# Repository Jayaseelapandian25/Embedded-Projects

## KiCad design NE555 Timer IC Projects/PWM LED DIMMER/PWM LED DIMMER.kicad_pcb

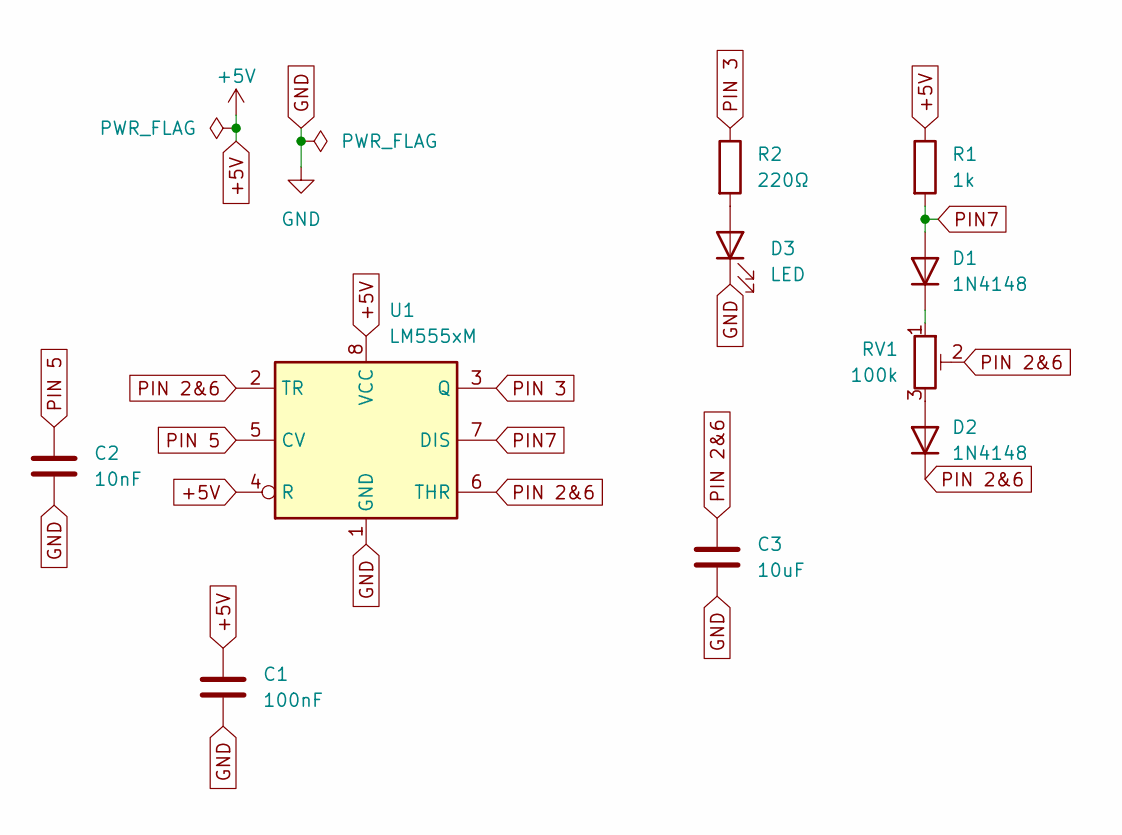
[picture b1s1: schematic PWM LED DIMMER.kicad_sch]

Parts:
C1: 100nF; C_0805_2012Metric_Pad1.18x1.45mm_HandSolder
C2: 10nF; C_0805_2012Metric_Pad1.18x1.45mm_HandSolder
C3: 10uF; C_0805_2012Metric_Pad1.18x1.45mm_HandSolder
D1, D2: 1N4148; D_SOD-123
D3: LED; LED_0805_2012Metric_Pad1.15x1.40mm_HandSolder
R1: 1k; R_0805_2012Metric_Pad1.20x1.40mm_HandSolder
R2: 220Ω; R_0805_2012Metric_Pad1.20x1.40mm_HandSolder
RV1: 100k; Potentiometer_Bourns_3296W_Vertical
U1: LM555xM; SOIC-8_3.9x4.9mm_P1.27mm

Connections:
+5V: C1.1, R1.1, U1.4 (R), U1.8 (VCC)
GND: C1.2, C2.2, C3.2, D3.1 (K), U1.1 (GND)
unnamed: D1.1 (K), RV1.1
unnamed: D2.2 (A), RV1.3
unnamed: D3.2 (A), R2.2
PIN7: D1.2 (A), R1.2, U1.7 (DIS)
PIN 2&6: C3.1, D2.1 (K), RV1.2, U1.2 (TR), U1.6 (THR)
PIN 3: R2.1, U1.3 (Q)
PIN 5: C2.1, U1.5 (CV)

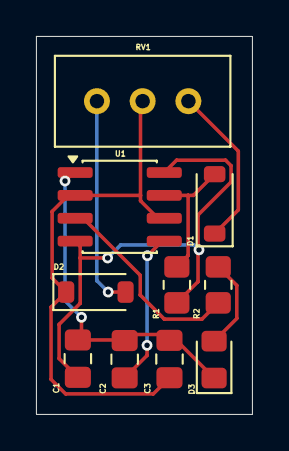
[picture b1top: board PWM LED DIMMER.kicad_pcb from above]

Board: 2 copper layers, 12.0 x 21.0 mm, 10 parts (0 on the bottom side), 9 nets.

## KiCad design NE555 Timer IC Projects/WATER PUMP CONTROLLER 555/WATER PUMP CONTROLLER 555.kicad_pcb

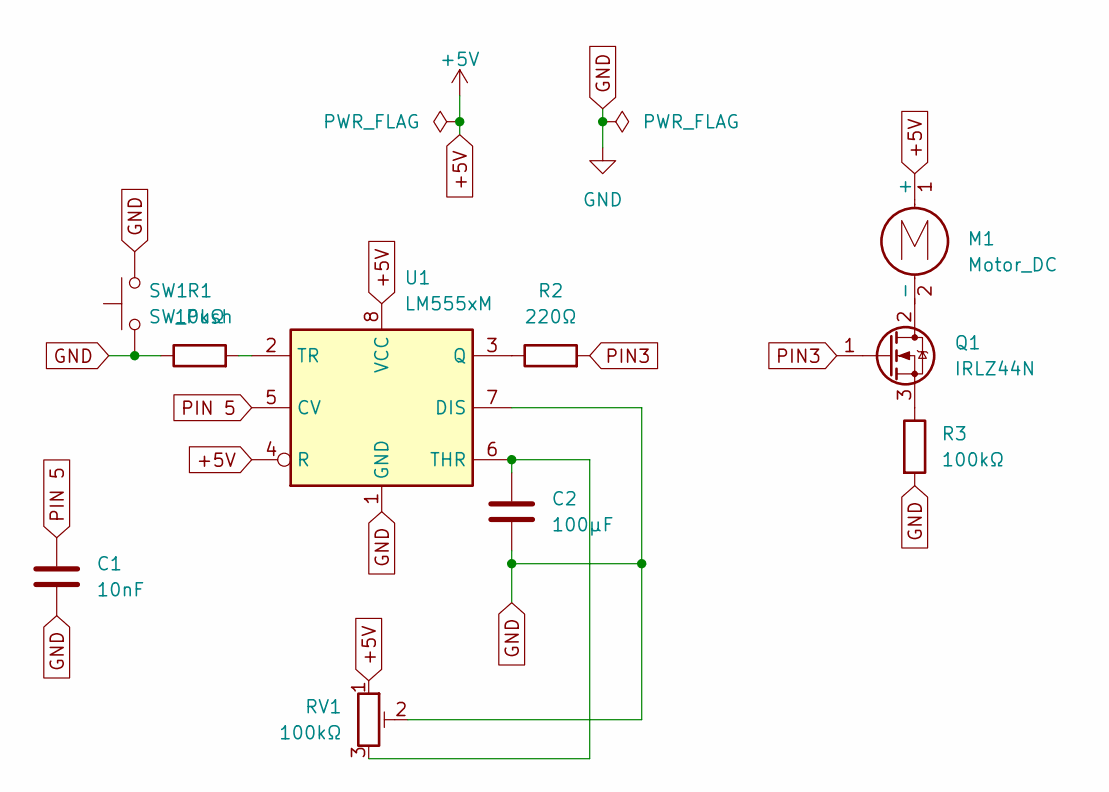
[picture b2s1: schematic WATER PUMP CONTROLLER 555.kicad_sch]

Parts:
C1: 10nF; C_0805_2012Metric
C2: 100µF; C_0805_2012Metric
M1: Motor_DC; JST_PH_B2B-PH-K_1x02_P2.00mm_Vertical
Q1: IRLZ44N; TO-220-3_Vertical
R1: 10kΩ; R_0805_2012Metric
R2: 220Ω; R_0805_2012Metric
R3: 100kΩ; R_0805_2012Metric
RV1: 100kΩ; Potentiometer_Bourns_3296W_Vertical
SW1: SW_Push; SW_SPST_TL3342
U1: LM555xM; SOIC-8_3.9x4.9mm_P1.27mm

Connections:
+5V: M1.1 (+), RV1.1, U1.4 (R), U1.8 (VCC)
GND: C1.2, C2.2, R1.1, R3.2, RV1.2, SW1.1, SW1.2, U1.1 (GND), U1.7 (DIS)
unnamed: M1.2 (-), Q1.2 (D)
unnamed: Q1.3 (S), R3.1
unnamed: R2.1, U1.3 (Q)
unnamed: C2.1, RV1.3, U1.6 (THR)
unnamed: R1.2, U1.2 (TR)
PIN3: Q1.1 (G), R2.2
PIN 5: C1.1, U1.5 (CV)

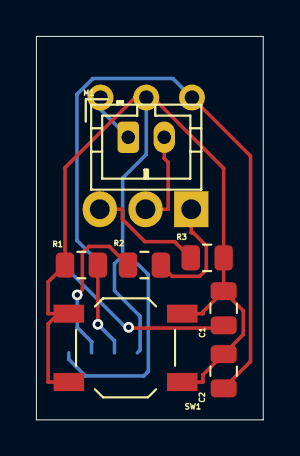
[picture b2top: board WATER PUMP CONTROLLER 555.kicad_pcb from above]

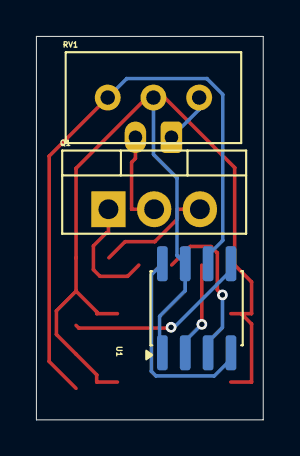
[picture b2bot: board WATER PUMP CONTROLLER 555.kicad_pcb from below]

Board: 2 copper layers, 12.6 x 21.3 mm, 10 parts (3 on the bottom side), 9 nets.

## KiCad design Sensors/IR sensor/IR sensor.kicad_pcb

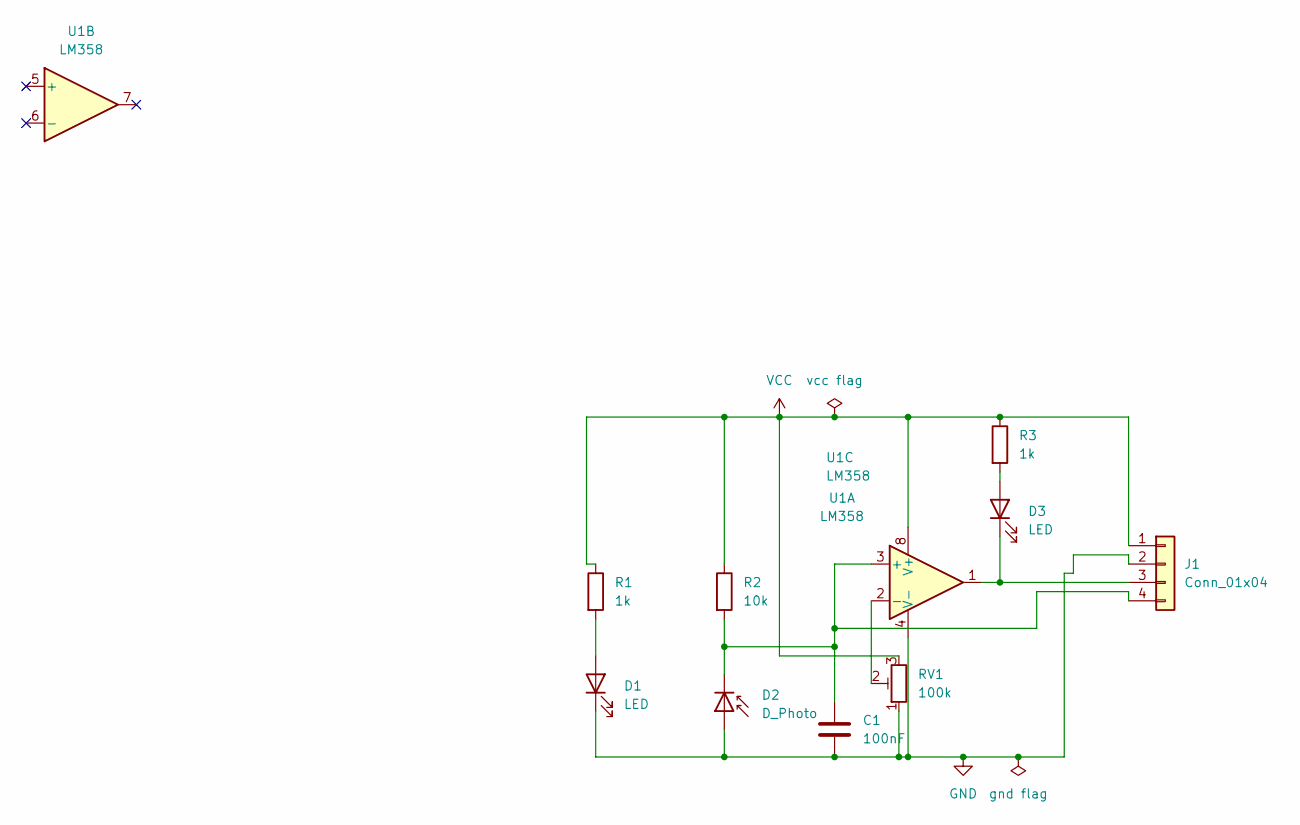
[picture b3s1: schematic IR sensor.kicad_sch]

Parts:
C1: 100nF; C_0805_2012Metric_Pad1.18x1.45mm_HandSolder
D1, D3: LED; LED_0805_2012Metric
D2: D_Photo; LED_D5.0mm
J1: Conn_01x04; PinHeader_1x04_P1.00mm_Vertical
R1, R3: 1k; R_0805_2012Metric_Pad1.20x1.40mm_HandSolder
R2: 10k; R_0805_2012Metric_Pad1.20x1.40mm_HandSolder
RV1: 100k; Potentiometer_Bourns_3296W_Vertical
U1: LM358; DIP-8_W7.62mm

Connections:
GND: C1.2, D1.1 (K), D2.2 (A), J1.2, RV1.1, U1.4 (V-)
unnamed: D1.2 (A), R1.2
unnamed: C1.1, D2.1 (K), J1.4, R2.2, U1.3 (+)
unnamed: D3.2 (A), R3.2
unnamed: D3.1 (K), J1.3, U1.1
unnamed: RV1.2, U1.2 (-)
VCC: J1.1, R1.1, R2.1, R3.1, RV1.3, U1.8 (V+)

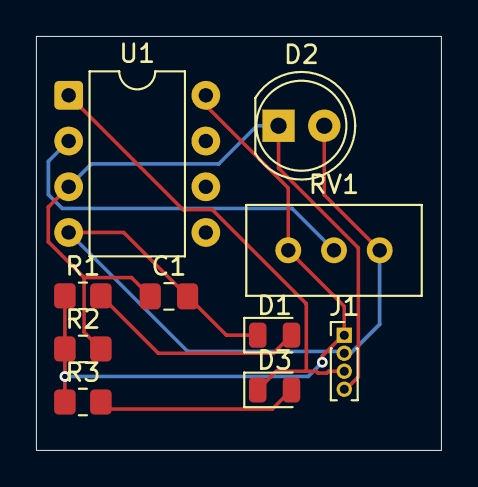
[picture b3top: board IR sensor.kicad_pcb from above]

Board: 2 copper layers, 22.5 x 23.0 mm, 10 parts (0 on the bottom side), 7 nets.

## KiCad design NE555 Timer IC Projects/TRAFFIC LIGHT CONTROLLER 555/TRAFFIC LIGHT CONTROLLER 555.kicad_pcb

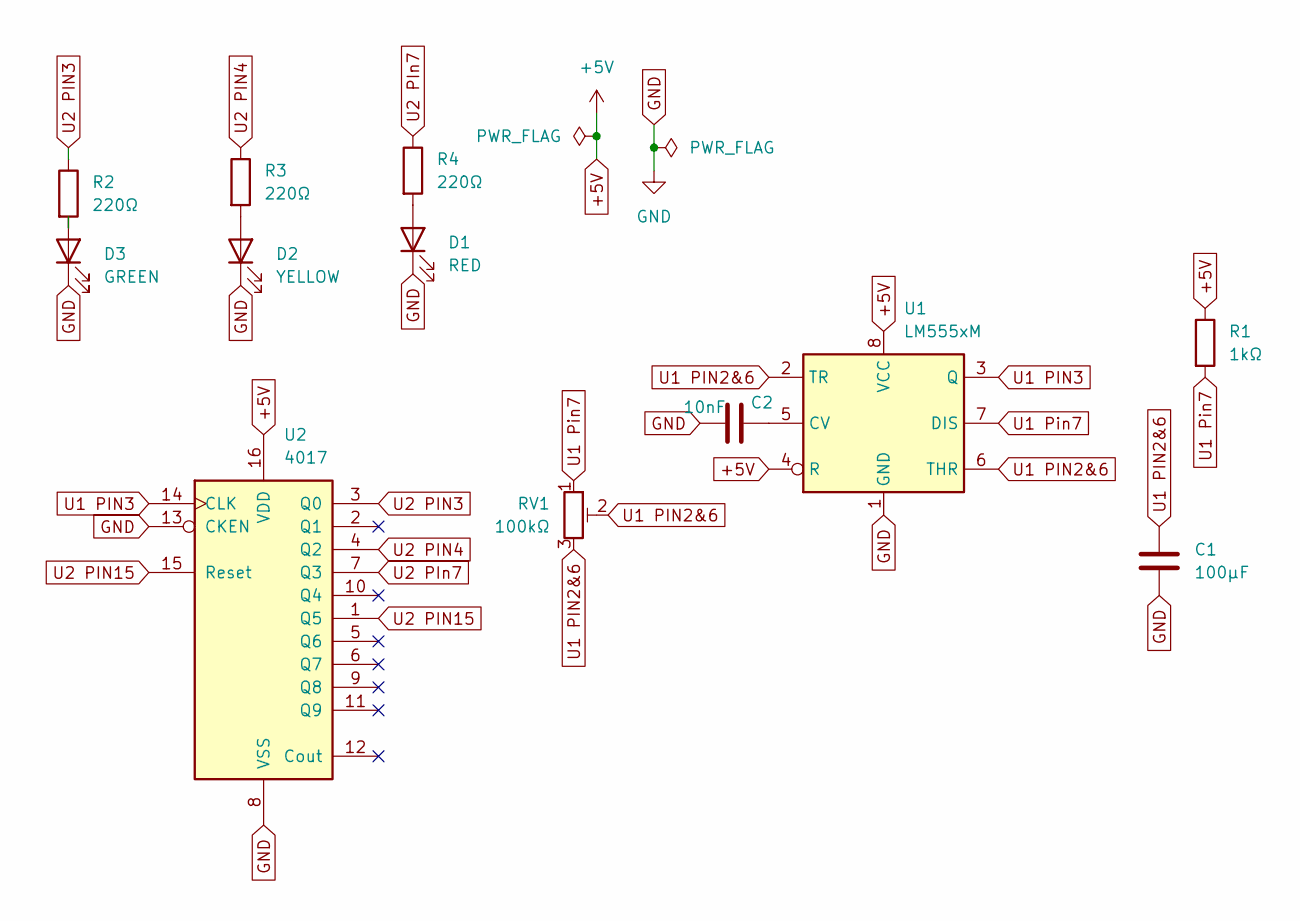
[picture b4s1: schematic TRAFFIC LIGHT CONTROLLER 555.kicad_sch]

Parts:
C1: 100µF; CP_Elec_5x5.4
C2: 10nF; C_0805_2012Metric
D1: RED; LED_0805_2012Metric
D2: YELLOW; LED_0805_2012Metric
D3: GREEN; LED_0805_2012Metric
R1: 1kΩ; R_0805_2012Metric
R2, R3, R4: 220Ω; R_0805_2012Metric
RV1: 100kΩ; Potentiometer_Bourns_3296W_Vertical
U1: LM555xM; SOIC-8_3.9x4.9mm_P1.27mm
U2: 4017; SOIC-16_3.9x9.9mm_P1.27mm

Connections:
+5V: R1.1, U1.4 (R), U1.8 (VCC), U2.16 (VDD)
GND: C1.2, C2.2, D1.1 (K), D2.1 (K), D3.1 (K), U1.1 (GND), U2.8 (VSS), U2.13 (CKEN)
unnamed: D1.2 (A), R4.2
unnamed: D2.2 (A), R3.2
unnamed: D3.2 (A), R2.2
unnamed: C2.1, U1.5 (CV)
U1 PIN2&6: C1.1, RV1.2, RV1.3, U1.2 (TR), U1.6 (THR)
U1 PIN3: U1.3 (Q), U2.14 (CLK)
U1 Pin7: R1.2, RV1.1, U1.7 (DIS)
U2 PIN3: R2.1, U2.3 (Q0)
U2 PIN4: R3.1, U2.4 (Q2)
U2 PIN15: U2.1 (Q5), U2.15 (Reset)
U2 PIn7: R4.1, U2.7 (Q3)

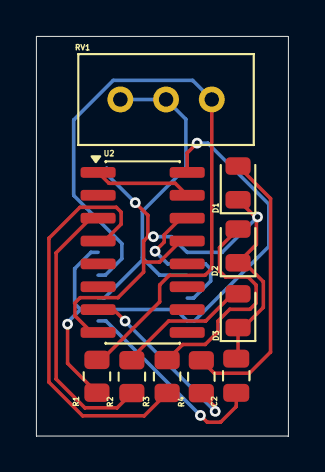
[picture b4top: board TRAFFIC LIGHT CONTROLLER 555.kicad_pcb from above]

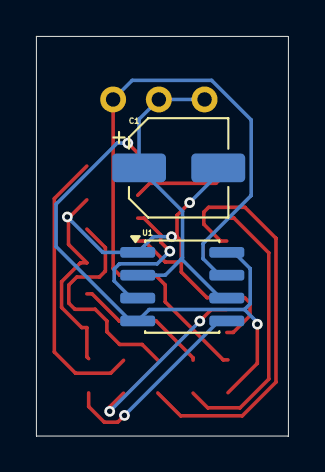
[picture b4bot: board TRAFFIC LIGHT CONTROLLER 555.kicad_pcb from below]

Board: 2 copper layers, 14.0 x 22.2 mm, 12 parts (2 on the bottom side), 13 nets.

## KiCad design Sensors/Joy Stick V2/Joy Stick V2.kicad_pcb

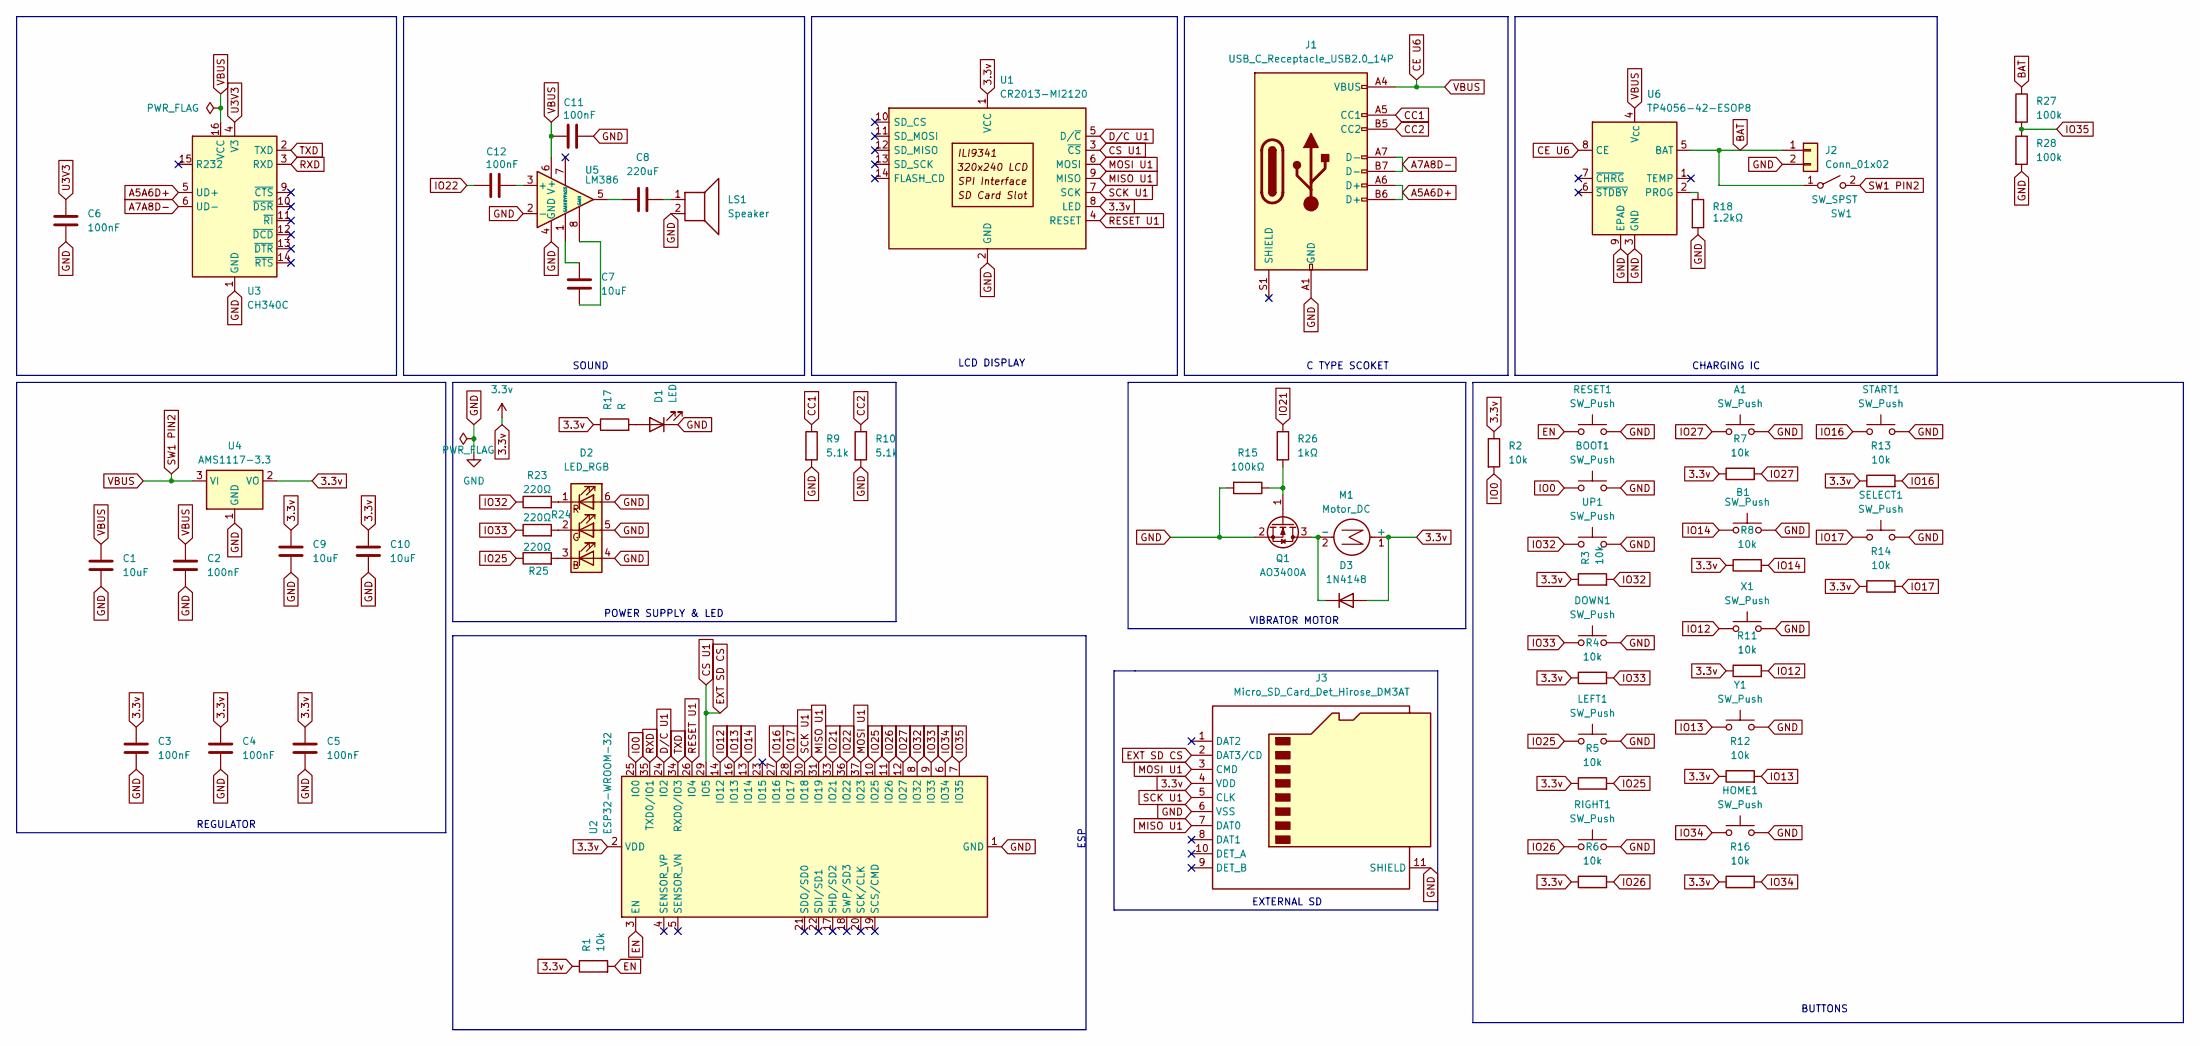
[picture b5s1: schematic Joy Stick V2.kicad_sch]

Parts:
A1: SW_Push; SW_SPST_TL3342
B1: SW_Push; SW_SPST_TL3342
BOOT1: SW_Push; SW_SPST_TL3342
C1, C7, C9, C10: 10uF; C_0805_2012Metric
C2, C3, C4, C5, C6, C11, C12: 100nF; C_0805_2012Metric
C8: 220uF; C_0805_2012Metric
D1: LED; LED_0805_2012Metric
D2: LED_RGB; LED_RGB_5050-6
D3: 1N4148; D_SOD-123
DOWN1: SW_Push; SW_SPST_TL3342
HOME1: SW_Push; SW_SPST_TL3342
J1: USB_C_Receptacle_USB2.0_14P; USB_C_Receptacle_HRO_TYPE-C-31-M-12
J2: Conn_01x02; JST_PH_S2B-PH-K_1x02_P2.00mm_Horizontal
J3: Micro_SD_Card_Det_Hirose_DM3AT; microSD_HC_Hirose_DM3AT-SF-PEJM5
LEFT1: SW_Push; SW_SPST_TL3342
LS1: Speaker; JST_PH_S2B-PH-K_1x02_P2.00mm_Horizontal
M1: Motor_DC; JST_PH_S2B-PH-K_1x02_P2.00mm_Horizontal
Q1: AO3400A; SOT-23
R1, R2, R3, R4, R5, R6, R7, R8, R11, R12, R13, R14, R16: 10k; R_0805_2012Metric
R9, R10: 5.1k; R_0805_2012Metric
R15: 100kΩ; R_0805_2012Metric
R17: R; R_0805_2012Metric
R18: 1.2kΩ; R_0805_2012Metric
R23, R24, R25: 220Ω; R_0805_2012Metric
R26: 1kΩ; R_0805_2012Metric
R27, R28: 100k; R_0805_2012Metric
RESET1: SW_Push; SW_SPST_TL3342
RIGHT1: SW_Push; SW_SPST_TL3342
SELECT1: SW_Push; SW_SPST_TL3342
START1: SW_Push; SW_SPST_TL3342
SW1: SW_SPST; SW_SPST_TL3342
U1: CR2013-MI2120
U2: ESP32-WROOM-32
U3: CH340C; SOIC-16_3.9x9.9mm_P1.27mm
U4: AMS1117-3.3; SOT-223-3_TabPin2
U5: LM386; SOIC-8_3.9x4.9mm_P1.27mm
U6: TP4056-42-ESOP8; SOIC-8-1EP_3.9x4.9mm_P1.27mm_EP2.41x3.3mm_ThermalVias
UP1: SW_Push; SW_SPST_TL3342
X1: SW_Push; SW_SPST_TL3342
Y1: SW_Push; SW_SPST_TL3342

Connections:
3.3v: C3.1, C4.1, C5.1, C9.1, C10.1, D3.2 (A), J3.4 (VDD), M1.1 (+), R1.1, R2.1, R3.1, R4.1, R5.1, R6.1, R7.1, R8.1, R11.1, R12.1, R13.1, R14.1, R16.1, R17.1, U1.1 (VCC), U1.8 (LED), U2.2 (VDD), U4.2 (VO)
A5A6D+: J1.A6 (D+), J1.B6 (D+), U3.5 (UD+)
A7A8D-: J1.A7 (D-), J1.B7 (D-), U3.6 (UD-)
BAT: J2.1, R27.1, SW1.1 (A), U6.5 (BAT)
CC1: J1.A5 (CC1), R9.1
CC2: J1.B5 (CC2), R10.1
CE U6: C1.1, C2.1, C11.1, J1.A4 (VBUS), J1.A9 (VBUS), J1.B4 (VBUS), J1.B9 (VBUS), SW1.2 (B), U3.16 (VCC), U4.3 (VI), U5.6 (V+), U6.4 (V_{CC}), U6.8 (CE)
CS U1: J3.2 (DAT3/CD), U1.3 (~CS), U2.29 (IO5)
D/C U1: U1.5 (D/~C), U2.24 (IO2)
EN: R1.2, RESET1.1, U2.3 (EN)
GND: A1.2, B1.2, BOOT1.2, C1.2, C2.2, C3.2, C4.2, C5.2, C6.2, C9.2, C10.2, C11.2, D1.1 (K), D2.4 (BA), D2.5 (GA), D2.6 (RA), DOWN1.2, HOME1.2, J1.A1 (GND), J1.A12 (GND), J1.B1 (GND), J1.B12 (GND), J2.2, J3.6 (VSS), J3.11 (SHIELD), LEFT1.2, LS1.2, Q1.2 (S), R9.2, R10.2, R15.2, R18.2, R28.2, RESET1.2, RIGHT1.2, SELECT1.2, START1.2, U1.2 (GND), U2.1 (GND), U2.15 (GND), U2.38 (GND), U2.39 (GND), U3.1 (GND), U4.1 (GND), U5.2 (-), U5.4 (GND), U6.3 (GND), U6.9 (EPAD), UP1.2, X1.2, Y1.2
IO0: BOOT1.1, R2.2, U2.25 (IO0)
IO12: R11.2, U2.14 (IO12), X1.1
IO13: R12.2, U2.16 (IO13), Y1.1
IO14: B1.1, R8.2, U2.13 (IO14)
IO16: R13.2, START1.1, U2.27 (IO16)
IO17: R14.2, SELECT1.1, U2.28 (IO17)
IO21: R26.1, U2.33 (IO21)
IO22: C12.1, U2.36 (IO22)
IO25: LEFT1.1, R5.2, R25.1, U2.10 (IO25)
IO26: R6.2, RIGHT1.1, U2.11 (IO26)
IO27: A1.1, R7.2, U2.12 (IO27)
IO32: R3.2, R23.1, U2.8 (IO32), UP1.1
IO33: DOWN1.1, R4.2, R24.1, U2.9 (IO33)
IO34: HOME1.1, R16.2, U2.6 (IO34)
IO35: R27.2, R28.1, U2.7 (IO35)
MISO U1: J3.7 (DAT0), U1.9 (MISO), U2.31 (IO19)
MOSI U1: J3.3 (CMD), U1.6 (MOSI), U2.37 (IO23)
unnamed: C7.1, U5.1 (GAIN)
unnamed: C7.2, U5.8 (GAIN)
unnamed: C8.1, U5.5
unnamed: C8.2, LS1.1
unnamed: D1.2 (A), R17.2
unnamed: D2.3 (BK), R25.2
unnamed: D2.2 (GK), R24.2
unnamed: D2.1 (RK), R23.2
unnamed: D3.1 (K), M1.2 (-), Q1.3 (D)
unnamed: Q1.1 (G), R15.1, R26.2
unnamed: C12.2, U5.3 (+)
unnamed: R18.1, U6.2 (PROG)
RESET U1: U1.4 (RESET), U2.26 (IO4)
RXD: U2.35 (TXD0/IO1), U3.3 (RXD)
SCK U1: J3.5 (CLK), U1.7 (SCK), U2.30 (IO18)
TXD: U2.34 (RXD0/IO3), U3.2 (TXD)
U3V3: C6.1, U3.4 (V3)

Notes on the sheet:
BUTTONS
POWER SUPPLY & LED
C TYPE SCOKET
CHARGING IC
VIBRATOR MOTOR
ESP
EXTERNAL SD
LCD DISPLAY
REGULATOR
SOUND

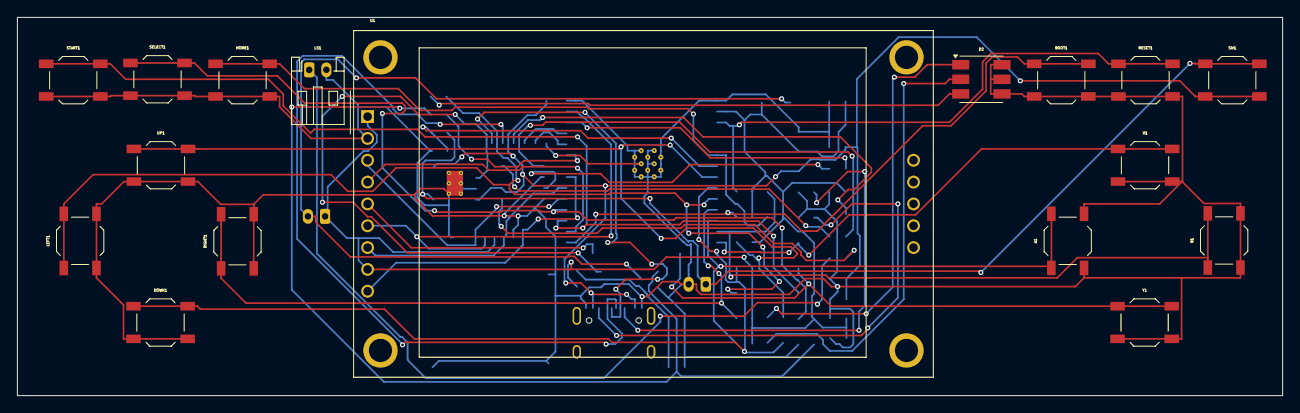
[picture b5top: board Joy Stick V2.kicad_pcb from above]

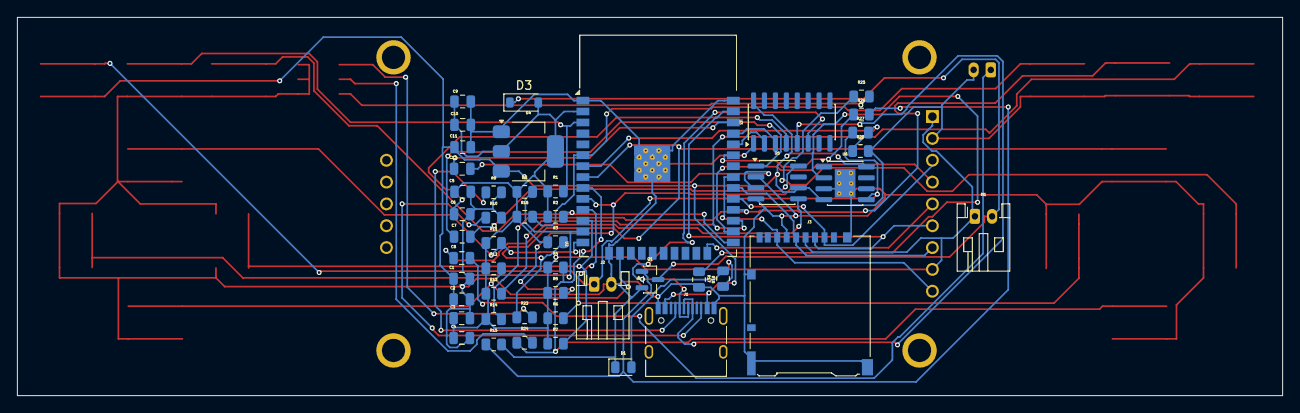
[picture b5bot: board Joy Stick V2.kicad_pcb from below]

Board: 2 copper layers, 147.2 x 44.0 mm, 65 parts (48 on the bottom side), 45 nets.

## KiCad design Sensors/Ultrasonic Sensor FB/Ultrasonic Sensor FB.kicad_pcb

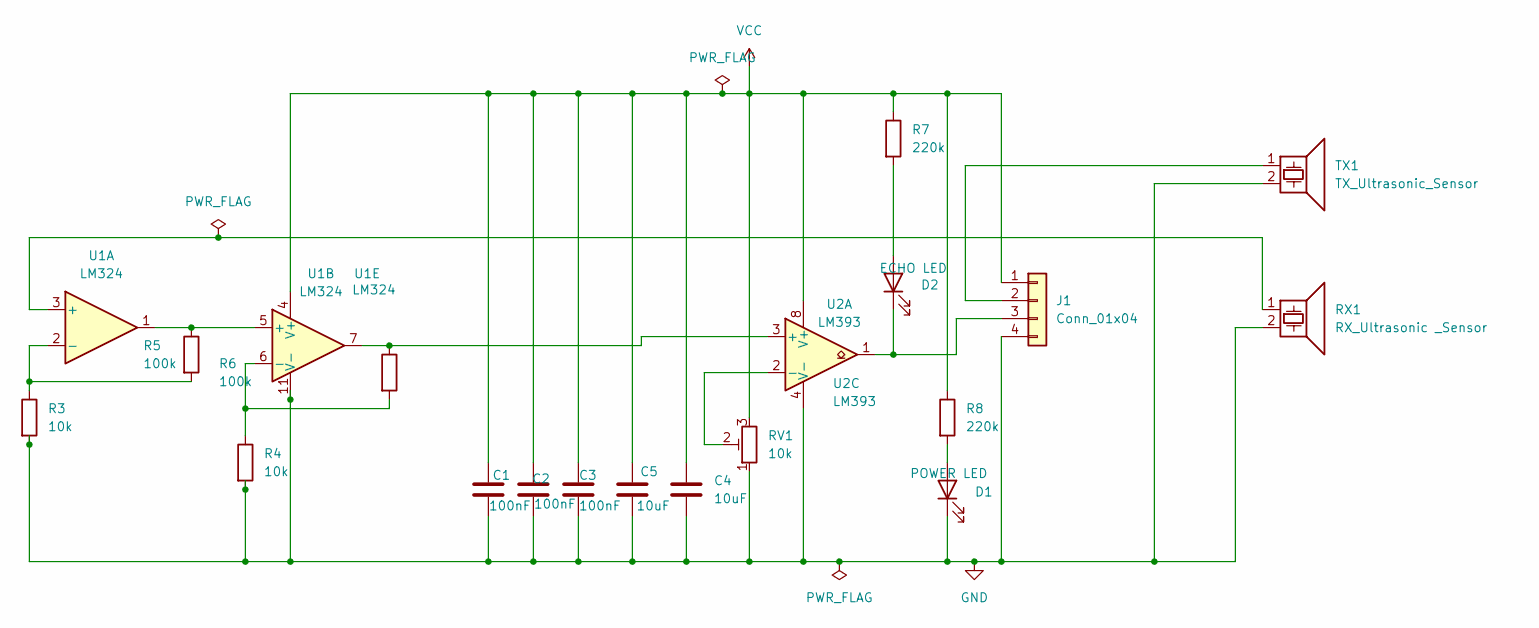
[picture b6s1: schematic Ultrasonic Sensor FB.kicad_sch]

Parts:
C1, C2, C3: 100nF; C_0805_2012Metric_Pad1.18x1.45mm_HandSolder
C4, C5: 10uF; C_0805_2012Metric_Pad1.18x1.45mm_HandSolder
D1: POWER LED; LED_0805_2012Metric_Pad1.15x1.40mm_HandSolder
D2: ECHO LED; LED_0805_2012Metric_Pad1.15x1.40mm_HandSolder
J1: Conn_01x04; PinHeader_1x04_P2.54mm_Vertical
R3, R4: 10k; R_0805_2012Metric_Pad1.20x1.40mm_HandSolder
R5, R6: 100k; R_0805_2012Metric_Pad1.20x1.40mm_HandSolder
R7, R8: 220k; R_0805_2012Metric_Pad1.20x1.40mm_HandSolder
RV1: 10k; Potentiometer_Bourns_3214X_Vertical
RX1: RX_Ultrasonic _Sensor; Buzzer_12x9.5RM7.6
TX1: TX_Ultrasonic_Sensor; Buzzer_12x9.5RM7.6
U1: LM324; SOIC-14_3.9x8.7mm_P1.27mm
U2: LM393; SOIC-8_3.9x4.9mm_P1.27mm

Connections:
GND: C1.2, C2.2, C3.2, C4.2, C5.2, D1.1 (K), J1.4, R3.2, R4.2, RV1.1, RX1.2, TX1.2, U1.11 (V-), U2.4 (V-)
unnamed: D1.2 (A), R8.2
unnamed: D2.2 (A), R7.2
unnamed: D2.1 (K), J1.3, U2.1
unnamed: J1.2, TX1.1
unnamed: RX1.1, U1.3 (+)
unnamed: R3.1, R5.2, U1.2 (-)
unnamed: R5.1, U1.1, U1.5 (+)
unnamed: R4.1, R6.2, U1.6 (-)
unnamed: R6.1, U1.7, U2.3 (+)
unnamed: RV1.2, U2.2 (-)
VCC: C1.1, C2.1, C3.1, C4.1, C5.1, J1.1, R7.1, R8.1, RV1.3, U1.4 (V+), U2.8 (V+)

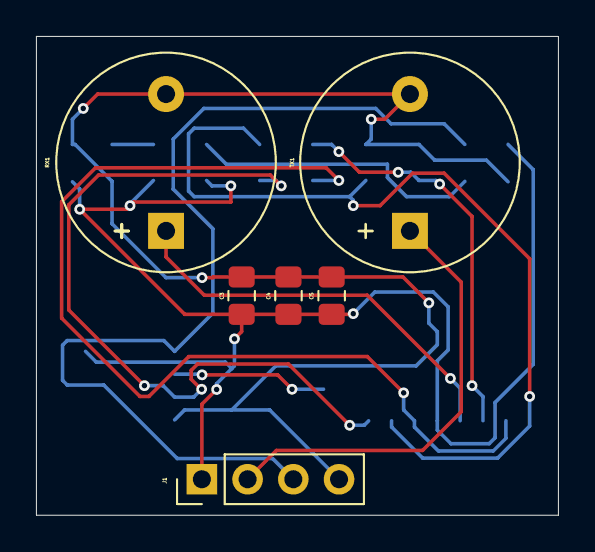
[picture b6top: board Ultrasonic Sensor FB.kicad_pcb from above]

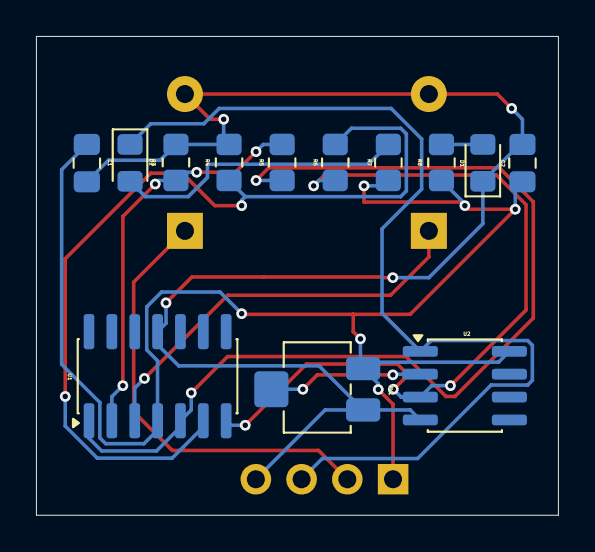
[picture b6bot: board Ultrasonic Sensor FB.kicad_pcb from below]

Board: 2 copper layers, 29.0 x 26.6 mm, 19 parts (13 on the bottom side), 12 nets.

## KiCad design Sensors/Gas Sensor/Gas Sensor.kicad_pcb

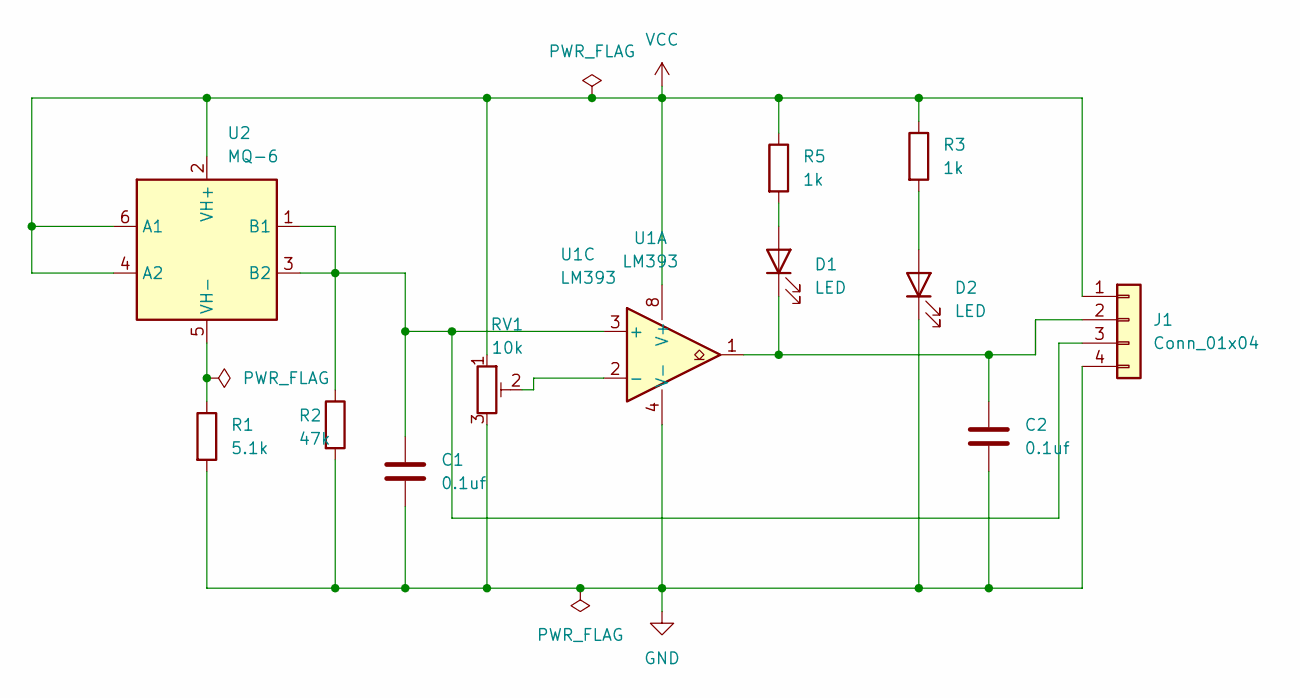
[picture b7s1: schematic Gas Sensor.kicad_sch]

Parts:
C1, C2: 0.1uf; C_0805_2012Metric_Pad1.18x1.45mm_HandSolder
D1, D2: LED; LED_0805_2012Metric_Pad1.15x1.40mm_HandSolder
J1: Conn_01x04; PinHeader_1x04_P2.54mm_Vertical_SMD_Pin1Left
R1: 5.1k; R_0805_2012Metric_Pad1.20x1.40mm_HandSolder
R2: 47k; R_0805_2012Metric_Pad1.20x1.40mm_HandSolder
R3, R5: 1k; R_0805_2012Metric_Pad1.20x1.40mm_HandSolder
RV1: 10k; Potentiometer_Bourns_3214X_Vertical
U1: LM393; SOIC-8_3.9x4.9mm_P1.27mm
U2: MQ-6

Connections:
GND: C1.2, C2.2, D2.1 (K), J1.4, R1.2, R2.2, RV1.3, U1.4 (V-)
unnamed: D1.2 (A), R5.2
unnamed: C2.1, D1.1 (K), J1.2, U1.1
unnamed: D2.2 (A), R3.2
unnamed: C1.1, J1.3, R2.1, U1.3 (+), U2.1 (B1), U2.3 (B2)
unnamed: RV1.2, U1.2 (-)
unnamed: R1.1, U2.5 (VH-)
VCC: J1.1, R3.1, R5.1, RV1.1, U1.8 (V+), U2.2 (VH+), U2.4 (A2), U2.6 (A1)

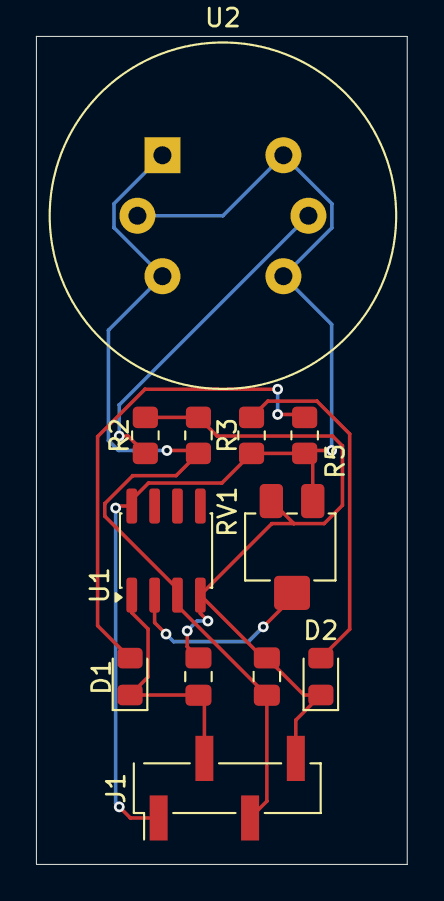
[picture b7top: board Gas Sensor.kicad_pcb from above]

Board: 2 copper layers, 20.6 x 46.0 mm, 12 parts (0 on the bottom side), 8 nets.

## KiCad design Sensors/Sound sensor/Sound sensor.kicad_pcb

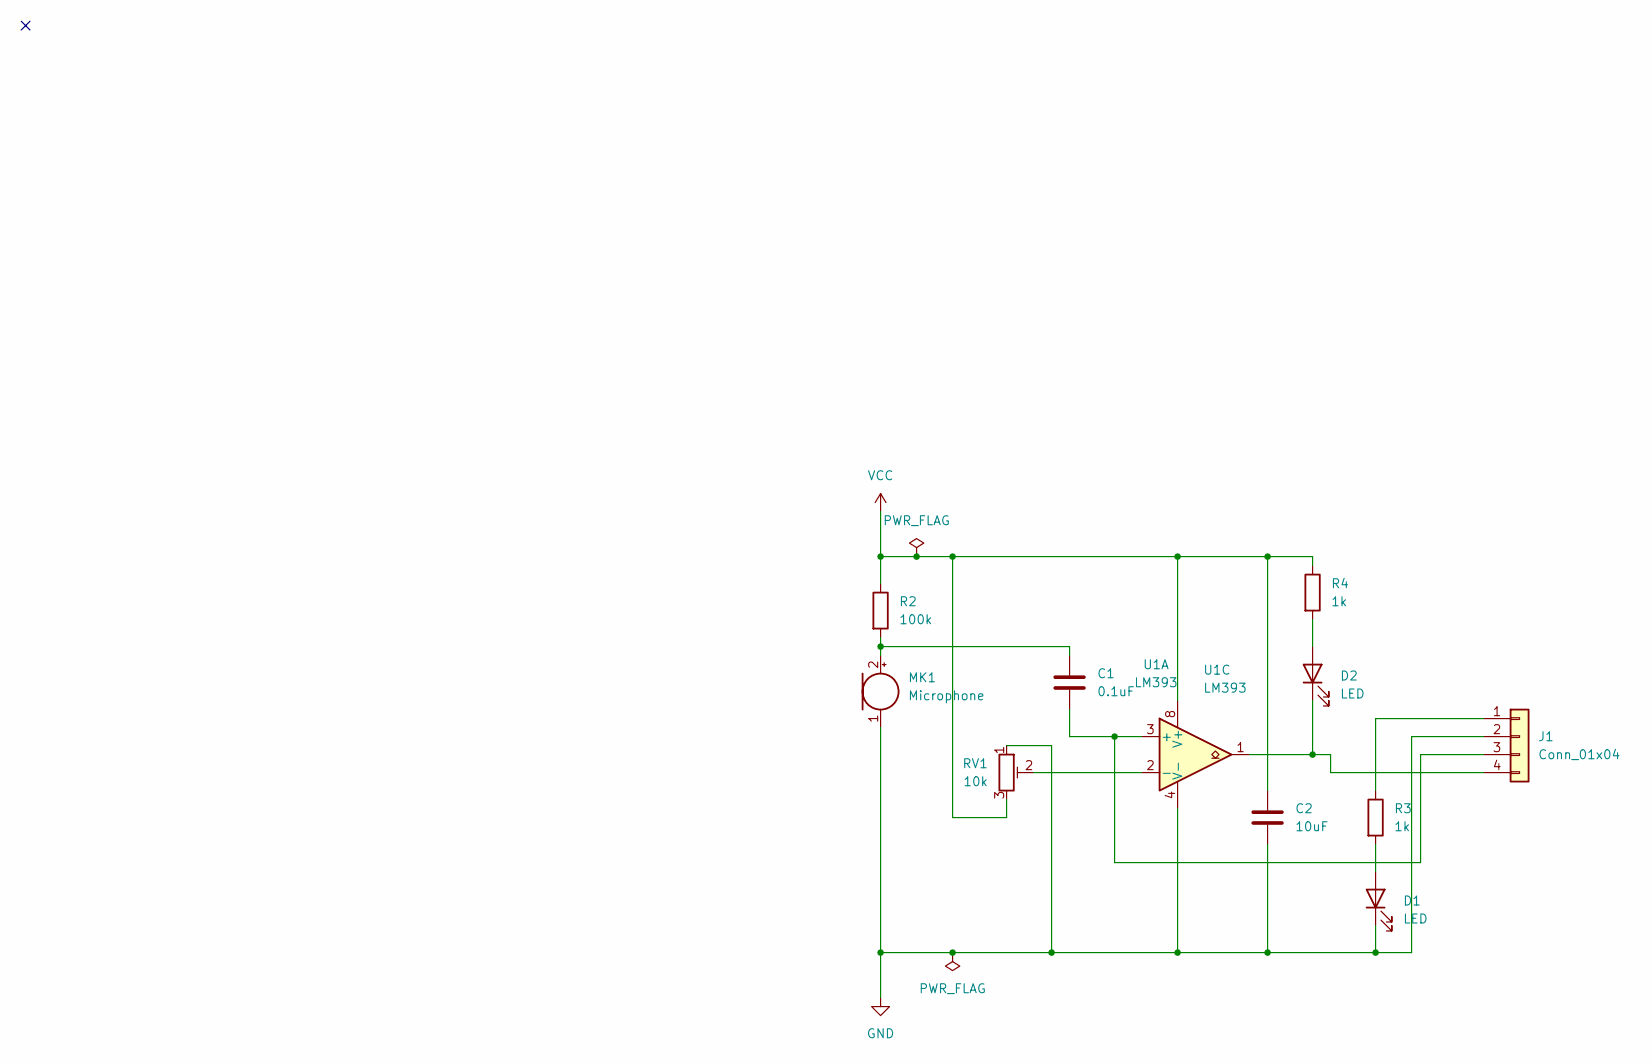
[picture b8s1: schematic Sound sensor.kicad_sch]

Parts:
C1: 0.1uF; C_0805_2012Metric_Pad1.18x1.45mm_HandSolder
C2: 10uF; C_0805_2012Metric_Pad1.18x1.45mm_HandSolder
D1, D2: LED; LED_0805_2012Metric_Pad1.15x1.40mm_HandSolder
J1: Conn_01x04; PinHeader_1x04_P2.54mm_Vertical
MK1: Microphone; PinHeader_1x02_P2.54mm_Vertical
R2: 100k; R_0805_2012Metric_Pad1.20x1.40mm_HandSolder
R3, R4: 1k; R_0805_2012Metric_Pad1.20x1.40mm_HandSolder
RV1: 10k; Potentiometer_Bourns_3214X_Vertical
U1: LM393; SOIC-8_3.9x4.9mm_P1.27mm

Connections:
GND: C2.2, D1.1 (K), J1.2, MK1.1 (-), RV1.1, U1.4 (V-)
unnamed: D1.2 (A), R3.2
unnamed: D2.2 (A), R4.2
unnamed: D2.1 (K), J1.4, U1.1
unnamed: J1.1, R3.1
unnamed: C1.2, J1.3, U1.3 (+)
unnamed: C1.1, MK1.2 (+), R2.2
unnamed: RV1.2, U1.2 (-)
VCC: C2.1, R2.1, R4.1, RV1.3, U1.8 (V+)

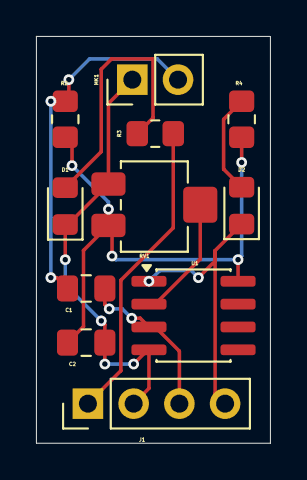
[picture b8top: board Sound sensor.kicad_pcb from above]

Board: 2 copper layers, 13.0 x 22.6 mm, 11 parts (0 on the bottom side), 9 nets.
